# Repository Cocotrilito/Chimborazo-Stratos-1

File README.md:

# Chimborazo-Stratos-1 V2
"Designed at the world's closest point to the stars." - me =p A custom Model Rocket Flight Computer (CFC) designed for high-altitude stabilization and recovery. It features an IMU for orientation tracking and a barometer for apogee detection. The goal is to create a reliable, low-cost brain for amateur rocketry in Ecuador.
## The reason behind this project
**"When something is important enough, you do it even if the odds are not in your favor."** *— Elon Musk*
This project is born with the intent of giving my homecountry a posibility or even a first step to develop new technology, maybe *inspire* others just like Astrounauts or cientifics inspired me.
## It's Alive!

First bring-up worked. The IMU and the barometer both came up on I2C at `0x68` and `0x77`, and the board is now streaming live telemetry over serial at 115200 baud.

Ground pressure read **75207 Pa**. Sea level is 101325 Pa, so the board is literally measuring the real atmosphere of Quito at ~2800m. Altitude noise is around ±0.1m, which is good enough for apogee detection.

The flight state machine goes `ARMED → BOOST → COAST → APOGEE → DESCENT`. Liftoff fires on an acceleration spike above 25 m/s², apogee on a 2m drop from peak altitude. Sensors are read at 50Hz and the dashboard prints every 3 seconds.
## Schematic Overview

## PCB

<table>
  <tr>
    <td width="50%"></td>
    <td width="50%"></td>
  </tr>
  <tr>
    <td align="center"><b>Front Copper</b></td>
    <td align="center"><b>Back Copper</b></td>
  </tr>
</table>

## CAD MODEL

<table>
  <tr>
    <td width="50%"></td>
    <td width="50%"></td>
  </tr>
  <tr>
    <td align="center"><b>Side View</b></td>
    <td align="center"><b>Top View</b></td>
  </tr>
</table>

## Bom 
| Name | Purpose | Qty | Total Cost (USD) | Link |
| :--- | :--- | :---: | :---: | :--- |
| **XIAO ESP32-C6** | Main Flight Computer / MCU | 1 | $11.08 | [AliExpress](https://www.aliexpress.com/item/3256808627180483.html) |
| **GY-87 10DOF** | IMU & Barometer (Orientation/Altitude) | 1 | $1.53 | [AliExpress](https://www.aliexpress.com/item/3256807064707842.html) |
| **ATGM336H GPS** | Global Positioning System Module | 1 | $1.93 | [AliExpress](https://www.aliexpress.com/item/3256810342214632.html) |
| **SG90 Servos (2pcs)** | Canard Actuators (Active Stabilization) | 1 | $1.33 | [AliExpress](https://www.aliexpress.com/item/3256807031850814.html) |
| **JST PH 2.0 Connectors** | LiPo Battery Connection Set | 1 | $1.53 | [AliExpress](https://www.aliexpress.com/item/3256808243626691.html) |
| **40-Pin Headers (M/F)** | Interconnection & Sensor Mounting | 1 | $0.93 | [AliExpress](https://www.aliexpress.com/item/3256811594914967.html) |
| **JLCPCB PCBA** | PCB Manufacturing + SMT Assembly | 1 | $22.46 | [JLCPCB](https://jlcpcb.com) |
## Things I learned the hard way
- The GY-87 has 8 pins starting with `VCC_IN` but my PCB only breaks out 4. Turns out you can feed 3.3V straight into the `3V3` pin and skip the module's onboard regulator entirely. Left `VCC_IN` hanging off the edge and it worked.
- The SG90 servos were browning out my USB port on startup and killing my uploads. In flight they go on the LiPo, never on USB.
- This GY-87 ships with a **BMP180**, not a BMP280. Needs the `Adafruit_BMP085` library.
- The HMC5883L magnetometer hides behind the MPU6050's auxiliary bus. It only shows up at `0x1E` after enabling bypass mode with `INT_PIN_CFG = 0x02`.
## What's next
- [ ] Solder the JST PH 2.0 for the LiPo
- [ ] GPS satellite lock (UART is open, needs open sky)
- [ ] Servo control and canard stabilization
- [ ] Onboard flight data logging
## Final Notes
Thanks for reading! made possible with http://stasis.hackclub.com/
New version! after review
## Dreams
*By cocotrilo*
**made with luv <3**

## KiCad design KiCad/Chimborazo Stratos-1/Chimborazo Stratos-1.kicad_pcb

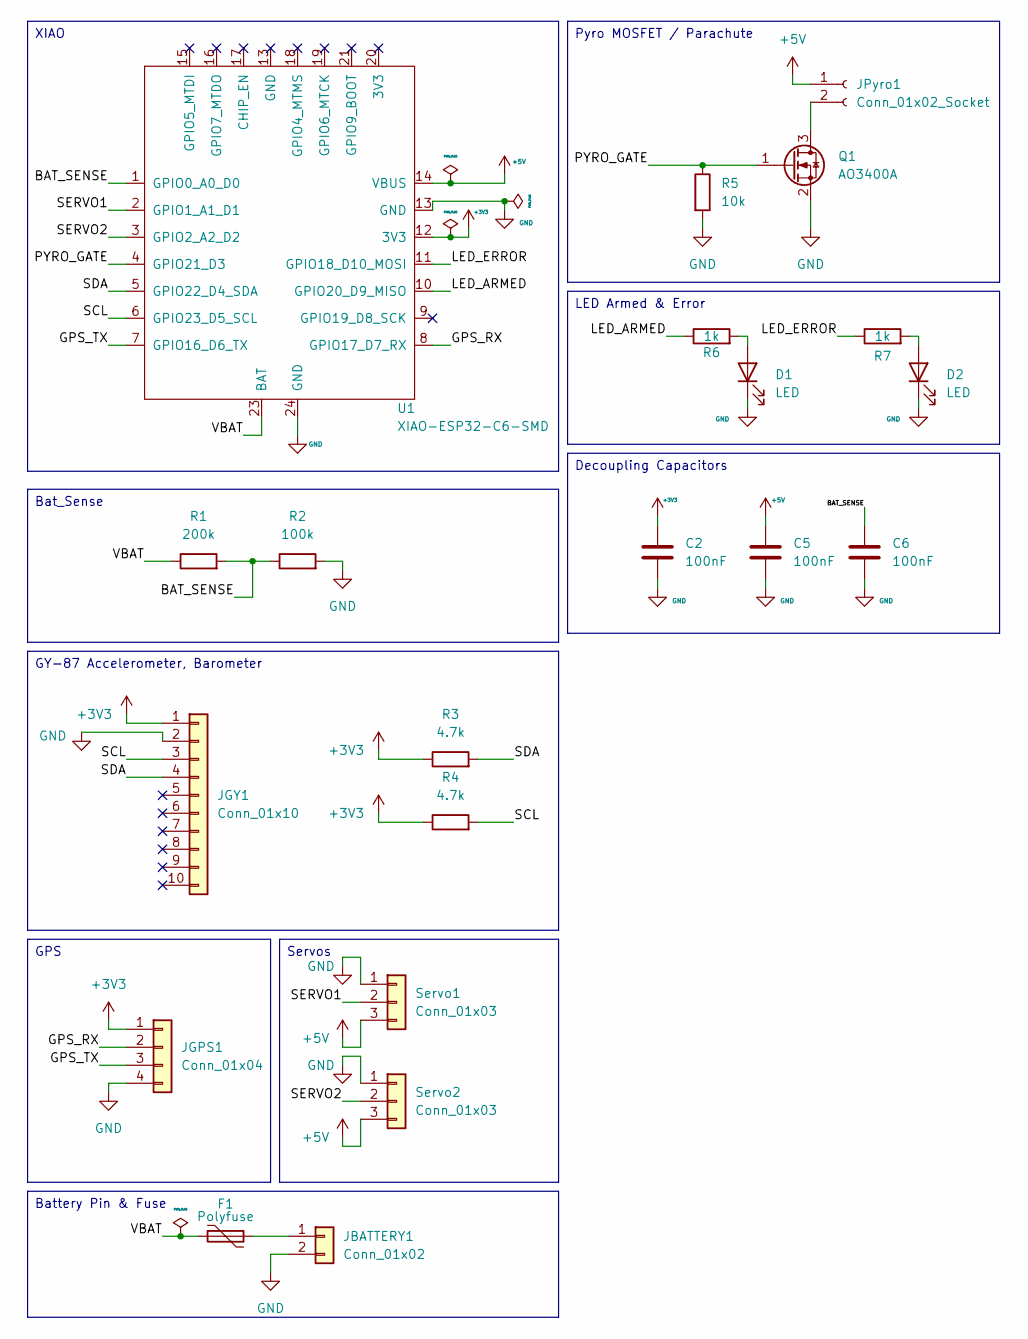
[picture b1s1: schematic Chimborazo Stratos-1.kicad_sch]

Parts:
C2, C5, C6: 100nF; C_0805_2012Metric
D1, D2: LED; LED_0805_2012Metric
F1: Polyfuse; Fuse_1206_3216Metric
JBATTERY1: Conn_01x02; JST_PH_B2B-PH-K_1x02_P2.00mm_Vertical
JGPS1: Conn_01x04; PinHeader_1x04_P2.54mm_Vertical
JGY1: Conn_01x10; PinHeader_1x10_P2.54mm_Vertical
JPyro1: Conn_01x02_Socket; PinHeader_1x02_P2.54mm_Vertical
Q1: AO3400A; SOT-23
R1: 200k; R_0805_2012Metric
R2: 100k; R_0805_2012Metric
R3, R4: 4.7k; R_0805_2012Metric
R5: 10k; R_0805_2012Metric
R6, R7: 1k; R_0805_2012Metric
Servo1, Servo2: Conn_01x03; PinHeader_1x03_P2.54mm_Vertical
U1: XIAO-ESP32-C6-SMD

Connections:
+3V3: C2.1, JGPS1.1, JGY1.1, R3.1, R4.1, U1.12 (3V3)
+5V: C5.1, JPyro1.1, Servo1.3, Servo2.3, U1.14 (VBUS)
/BAT_SENSE: C6.1, R1.2, R2.1, U1.1 (GPIO0_A0_D0)
/GPS_RX: JGPS1.2, U1.8 (GPIO17_D7_RX)
/GPS_TX: JGPS1.3, U1.7 (GPIO16_D6_TX)
/LED_ARMED: R6.1, U1.10 (GPIO20_D9_MISO)
/LED_ERROR: R7.1, U1.11 (GPIO18_D10_MOSI)
/PYRO_GATE: Q1.1 (G), R5.1, U1.4 (GPIO21_D3)
/SCL: JGY1.3, R4.2, U1.6 (GPIO23_D5_SCL)
/SDA: JGY1.4, R3.2, U1.5 (GPIO22_D4_SDA)
/SERVO1: Servo1.2, U1.2 (GPIO1_A1_D1)
/SERVO2: Servo2.2, U1.3 (GPIO2_A2_D2)
/VBAT: F1.1, R1.1, U1.23 (BAT)
GND: C2.2, C5.2, C6.2, D1.1 (K), D2.1 (K), JBATTERY1.2, JGPS1.4, JGY1.2, Q1.2 (S), R2.2, R5.2, Servo1.1, Servo2.1, U1.13 (GND), U1.24 (GND)
unnamed: D1.2 (A), R6.2
unnamed: D2.2 (A), R7.2
unnamed: F1.2, JBATTERY1.1
unnamed: JPyro1.2, Q1.3 (D)

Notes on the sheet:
Pyro MOSFET / Parachute
Servos
Bat_Sense
GY-87 Accelerometer, Barometer
Battery Pin & Fuse
XIAO
GPS
LED Armed & Error
Decoupling Capacitors

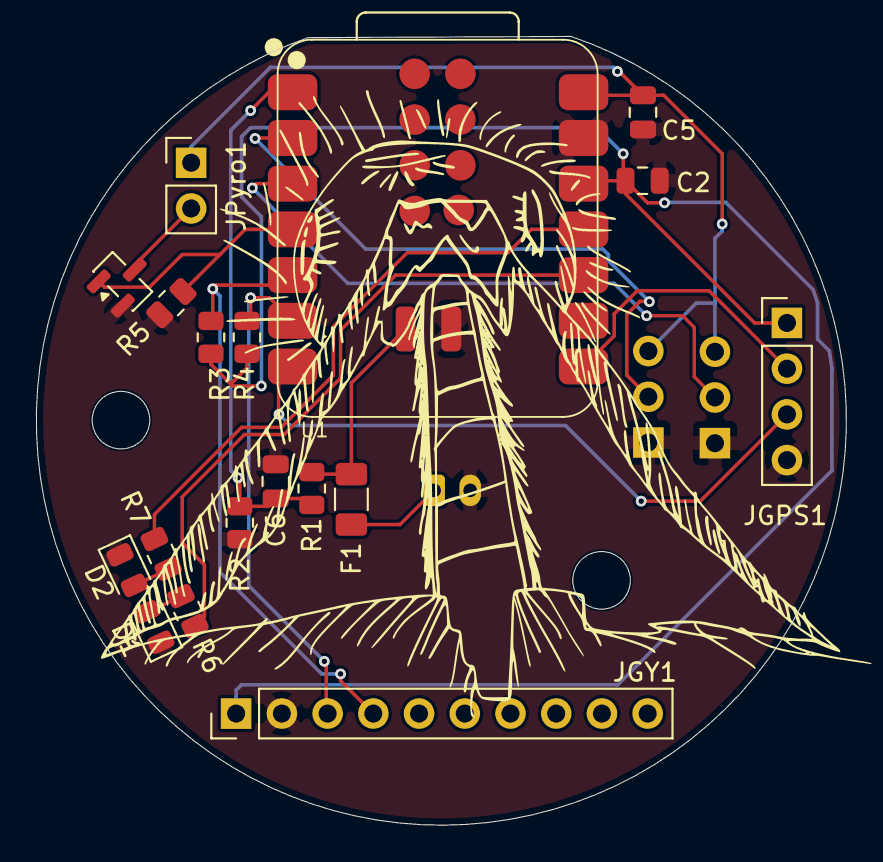
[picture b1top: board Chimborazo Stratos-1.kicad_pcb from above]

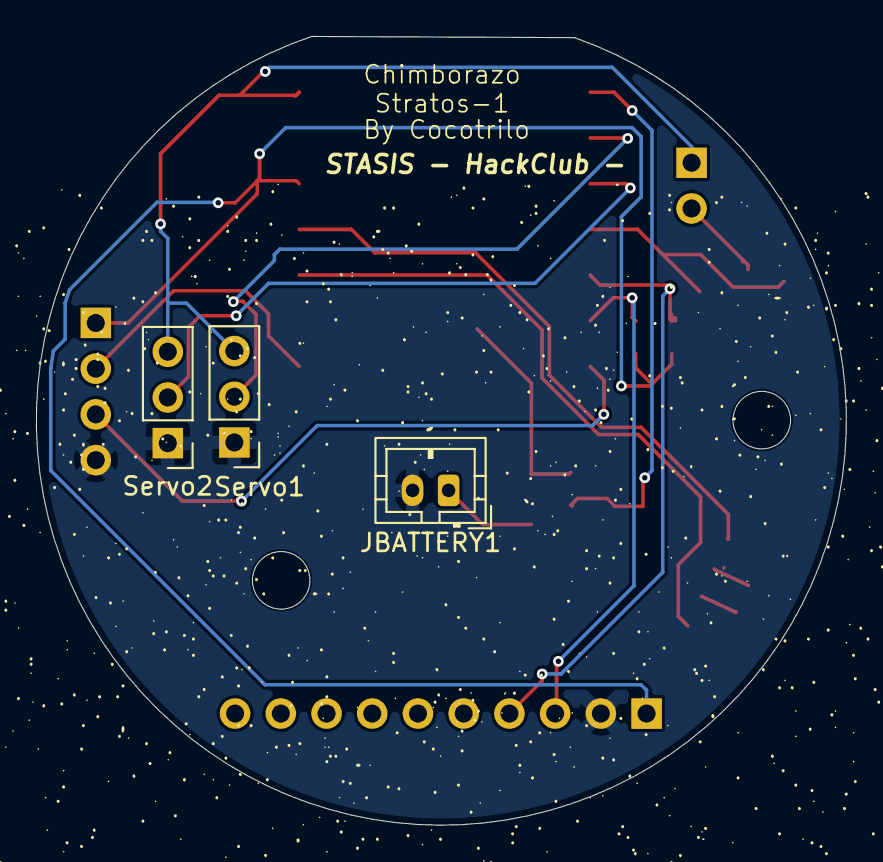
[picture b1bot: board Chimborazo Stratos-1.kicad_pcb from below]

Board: 2 copper layers, 45.0 x 43.8 mm, 21 parts (3 on the bottom side), 18 nets.

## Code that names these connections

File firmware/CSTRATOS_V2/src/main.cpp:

#include <Arduino.h>
#include <Wire.h>
#include <Adafruit_BMP085.h>
#include <ESP32Servo.h>
#include <MPU6050.h>


// pins
const int PIN_BAT_SENSE = 0;
const int PIN_SERVO1 = 1;
const int PIN_SERVO2 = 2;
const int PIN_PYRO = 21;
const int PIN_SDA = 22;
const int PIN_SCL = 23;
const int PIN_GPS_TX = 16;
const int PIN_GPS_RX = 17;
const int PIN_LED_ARMED = 20;
const int PIN_LED_ERROR = 18;

// altitude and ignition
float max_altitude = 0;
float ground_altitude = 0;
bool recovery_fired = false;


Adafruit_BMP085 bmp;
Servo servo1;
Servo servo2;
MPU6050 mpu;
int16_t ax, ay, az;
int16_t gx, gy, gz;

void setup() {
    Serial.begin(115200);
    pinMode(PIN_LED_ARMED, OUTPUT);
    pinMode(PIN_LED_ERROR, OUTPUT);
    pinMode(PIN_PYRO, OUTPUT);
    digitalWrite(PIN_PYRO, LOW);

    Wire.begin(PIN_SDA, PIN_SCL);
    delay(100);
    // BMP Altitude barometer
    if (!bmp.begin()) {
        digitalWrite(PIN_LED_ERROR, HIGH);
        Serial.println("Error No BMP");
        while (1);
    }

    float sum = 0;
    for(int i=0; i<10; i++) {
        sum += bmp.readAltitude();
        delay(50);
    }
    ground_altitude = sum / 10.0;

    // Accelerometer MPU6050
    Serial.println("Testing MPU");
    mpu.initialize();
    if (!mpu.testConnection()) {
        Serial.println("Error: MPU6050 no MPU");
        digitalWrite(PIN_LED_ERROR, HIGH);
    }
    // servos
    servo1.attach(PIN_SERVO1);
    servo2.attach(PIN_SERVO2);
    servo1.write(90); // 90 degrees
    servo2.write(90);

    // gps
    Serial1.begin(9600, SERIAL_8N1, PIN_GPS_RX, PIN_GPS_TX);

    digitalWrite(PIN_LED_ARMED, HIGH);
    Serial.println("System Ready");


}

void loop() {
    // bat sense
    int raw_bat = analogRead(PIN_BAT_SENSE);
    float voltage = (raw_bat / 4095.0) * 3.3 * 3.0;

    // altitude
    float current_alt = bmp.readAltitude();
    float relative_alt = current_alt - ground_altitude;

    if (relative_alt > max_altitude) {
        max_altitude = relative_alt;
    }

    // MPU
    mpu.getMotion6(&ax, &ay, &az, &gx, &gy, &gz);


    if (!recovery_fired) {
        // El Giroscopio nos da valores entre -32768 y 32767
        // Mapeamos el eje X (gx) para el Servo 1 y el eje Y (gy) para el Servo 2
        int angle1 = map(gx, -15000, 15000, 70, 110);
        int angle2 = map(gy, -15000, 15000, 70, 110);
        
        servo1.write(constrain(angle1, 70, 110));
        servo2.write(constrain(angle2, 70, 110));
    } else {
        // Si el paracaídas ya salió, ponemos los canards en posición neutral (90°)
        servo1.write(90);
        servo2.write(90);
    }

    if (max_altitude > 2.0 && (max_altitude - relative_alt) > 0.5 && !recovery_fired) {
        digitalWrite(PIN_PYRO, HIGH);
        Serial.println("!!DEPLOY!!");

        digitalWrite(PIN_LED_ARMED, LOW);
        digitalWrite(PIN_LED_ERROR, HIGH);

        delay(2000);
        digitalWrite(PIN_PYRO, LOW);
        recovery_fired = true;

    }

    Serial.printf("Alt: %.2f | Max: %.2f | Bat: %.2fV | Gx: %d\n", relative_alt, max_altitude, voltage, gx);
    
    if (voltage < 3.5) {
        digitalWrite(PIN_LED_ERROR, HIGH); 
    } else if (!recovery_fired) {
        digitalWrite(PIN_LED_ERROR, LOW);
    }

    delay(50);
}

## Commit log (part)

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2026-04-08 Organizing project structure and adding KiCad libraries and connecting to Github
2026-04-08 fixed long path errors and cleaned up libraries, finally I added the libs for the project it was REALLY HARD AND I DONT KNOW WHY :( but I managed to overcome the challenge
2026-04-08 Schematic prototype done
2026-04-09 PCB model 1 finalized
2026-04-09 Final PCB done!
2026-04-13 New PCB OF 45mm Diameter finished :)
2026-04-13 FORGOT TO ADD THE INFIL OF GND SORRYgit add .!
2026-04-14 Re-work of pcb and CAD model
2026-04-14 Finished the pcb and the cad model REAL NO FAKE
2026-04-14 Changed journal pics folder name to images
2026-04-14 Added the final photos
2026-04-15 Update README with schematic and model images
    Added schematic, PCB, and CAD model images to README.
2026-04-15 Renamed the images
2026-04-15 Reorganized folders and Added the GERBERS files
2026-04-15 ADDED THE FIRMWAREgit add .git add .!
2026-04-15 Final screenshots!
2026-04-15 FINAL COMMIT (i hope)
2026-04-15 Expand README with project motivation and dreams
    Added a section about the project's purpose and dreams.
2026-04-15 Everything ready for launch!
2026-04-29 Remade schmeatic changed components and Remade PCB with new and improved layout
2026-04-29 Update BOM section with new components and links
2026-04-29 Added BOM firmware, CAD, Schematic update, and more Images
2026-04-29 Revise README for Chimborazo-Stratos-1 V2
    Updated project details and images for version 2.
2026-04-29 Fix image references in README.md
    Corrected image filenames in README.md for B.cu and TOP.
